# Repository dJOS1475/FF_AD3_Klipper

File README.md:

# FlashForge Adventure 3 - Klipper + BTT SKR Mini E3 Upgrade

<p align="center">
  
</p>

Warning: this Upgrade is a Major effort and is recomended for Advanced 3D Printer Users with some electronics skills only. If you would like to keep your OEM mainboard and wiring, please see the Klippventure project by VioSynthax.

# 3D Printed items
are available via Printables:

https://www.printables.com/model/437968-flashforge-adventurer-3-klipper-revo-6-bltouch-btt

# Required Components:
* BigTree Tech SKR Mini E3 v3
* BigTree Tech TFT-35 MZ LCD Screen (with NoTouch E3 Firmware installed)
* PCB's: AD3 HE and AD3 HE BreakOut Boards.
* E3D Revo 6 Hot End
* Good Quality Ribbon cable - ~1.5 meters
* 2x9 Pin IDC Cable Connectors and sockets
* 2x Molex, Micro-Fit 3.0, 43650, 2 Way, 1 Row, Right Angle PCB Headers
* Assorted JST-PH PCB Sockets and Cable Connectors
* 2x PCB Mount Screw Terminal Blocks eg CUI Devices TB004-508-02BE
* 24v to 5v voltage converter eg "1PZ VAC-H15" to power your Raspberry Pi
* Printed Parts

# UPDATES:
* 12th April 2023 - fixed filament macros - please see the Filament_Sensor.cfg file for prerequisites  
* 2nd April 2023 - reduced max speed to 100mm/s - any higher results in layer shifts due to the temps getting too high for the stock stepper motors (at least while printing high tempmaterials like ASA)
* 1st April 2023 - Tweaks to max speed and driver current - the steppers don't seem to like travel speeds over 150mm/s without overheating and causing layer shifts
* 31st March 2023 - Printer now calibrated and Printer.cfg has been updated.
* 30th March 2023 - Everything now works! 

# Videos
FlashForge Adventurer 3 gets a new Brain, Hot-End and Klipper:
https://youtu.be/USZoIhBnA24

Sensorless Homing in Action:
https://youtu.be/0Acrmv7VkdY

and Printing ASA:
https://youtu.be/akCvX6l-e6o

# Klipper Features in use:
* Sensorless Homing
* Adaptive Purge
* Adaptive Mesh Levelling w/ BLTouch
* Auto-Load Filament using Filament Sensor
* Auto Unload Filament when run-out detected
* Unload macro for when you just want to change Filament types/colours etc
* Auto-Extraction Fan at the end of Print (via End G-Code)
* Working LED lighting

# NOTE: 
The factory belt tension on this printer is too loose to exceed 1k acceleration and 100mm/s print speeds. To rectify this you need to retension the X and Y axis belts properly (tight is good, but dont over do it). The Y axis is a PITA as it can only be fixed when the printer is fully disassembled. The Y belt is a continuous loop with no tension adjuster. So you'll need to cut out roughly 5mm from the belt and re-install it as snug as you can get it. I then used some "Selly's Power Grip" to ensure the belts dont jump out of the jaws holding them.

If you still have Y axis layer shifting, I recommend replacing the motor with a better quality unit.

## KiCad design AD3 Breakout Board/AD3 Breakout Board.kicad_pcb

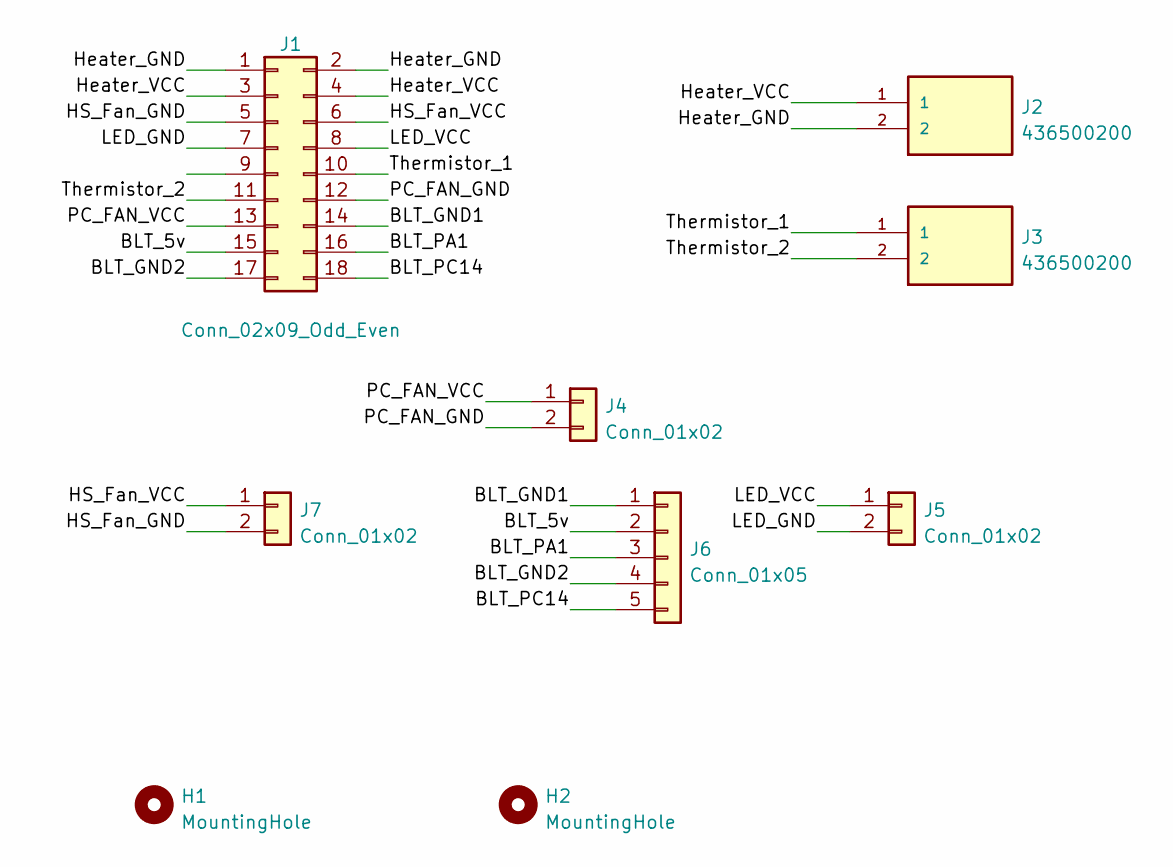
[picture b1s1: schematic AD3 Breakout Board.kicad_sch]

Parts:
H1, H2: MountingHole; MountingHole_3.2mm_M3_Custom_Pad
J1: Conn_02x09_Odd_Even; PinHeader_2x09_P2.54mm_Vertical
J2, J3: 436500200; TerminalBlock_Phoenix_MKDS-1,5-2-5.08_1x02_P5.08mm_Horizont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; PARTREV D7
J4, J5, J7: Conn_01x02; JST_PH_B2B-PH-K_1x02_P2.00mm_Vertical
J6: Conn_01x05; JST_PH_B5B-PH-K_1x05_P2.00mm_Vertical

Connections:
/BLT_5v: J1.15, J6.2
/BLT_GND1: J1.14, J6.1
/BLT_GND2: J1.17, J6.4
/BLT_PA1: J1.16, J6.3
/BLT_PC14: J1.18, J6.5
/HS_Fan_GND: J1.5, J7.2
/HS_Fan_VCC: J1.6, J7.1
/Heater_GND: J1.1, J1.2, J2.2
/Heater_VCC: J1.3, J1.4, J2.1
/LED_GND: J1.7, J5.2
/LED_VCC: J1.8, J5.1
/PC_FAN_GND: J1.12, J4.2
/PC_FAN_VCC: J1.13, J4.1
/Thermistor_1: J1.10, J3.1
/Thermistor_2: J1.11, J3.2

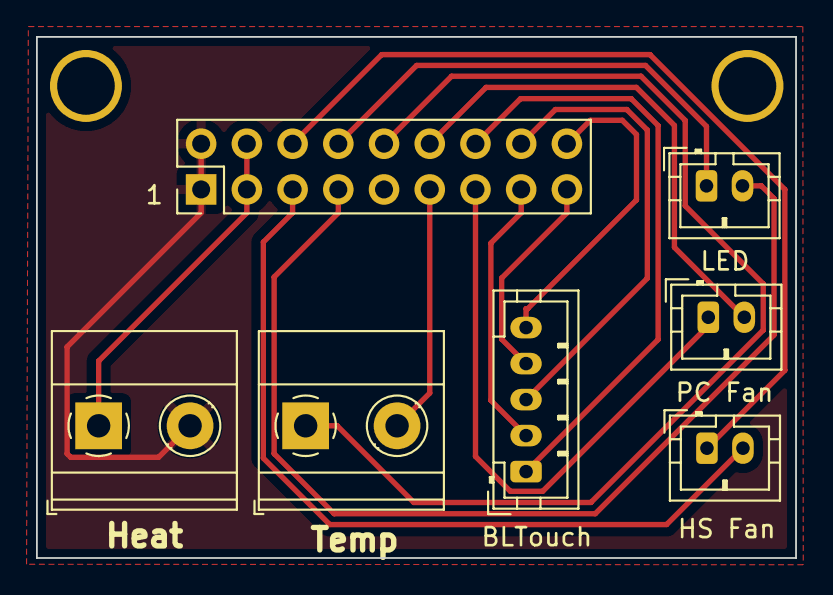
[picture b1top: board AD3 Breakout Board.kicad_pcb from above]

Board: 2 copper layers, 42.2 x 28.9 mm, 9 parts (0 on the bottom side), 15 nets.

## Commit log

2023-03-24 Add files via upload
    HE BreakOut Board
2023-03-24 Add files via upload
    HE Board
2023-03-24 Add files via upload
    Klipper Base Config
2023-03-24 Add files via upload
    Update Printer.cfg with stepper tweaks
2023-03-24 Update printer.cfg
    tweaked sensorless homing
2023-03-30 Add files via upload
    Sensorless Homing now Works
2023-04-02 Update printer.cfg
    Updated Speed limits
2023-04-12 Add files via upload
    Updates
2023-07-19 Update macros.cfg
    fixed homing config for stepper current in Y axis
